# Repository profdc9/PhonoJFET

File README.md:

# Phono JFET Amplifier

This is a JFET amplifier suitable to be used with a piezo contact microphone.  It is being used with a mechanical record player, but it can also be used with as a contact microphone on an acoustic guitar, the brass bell of a horn, etc.

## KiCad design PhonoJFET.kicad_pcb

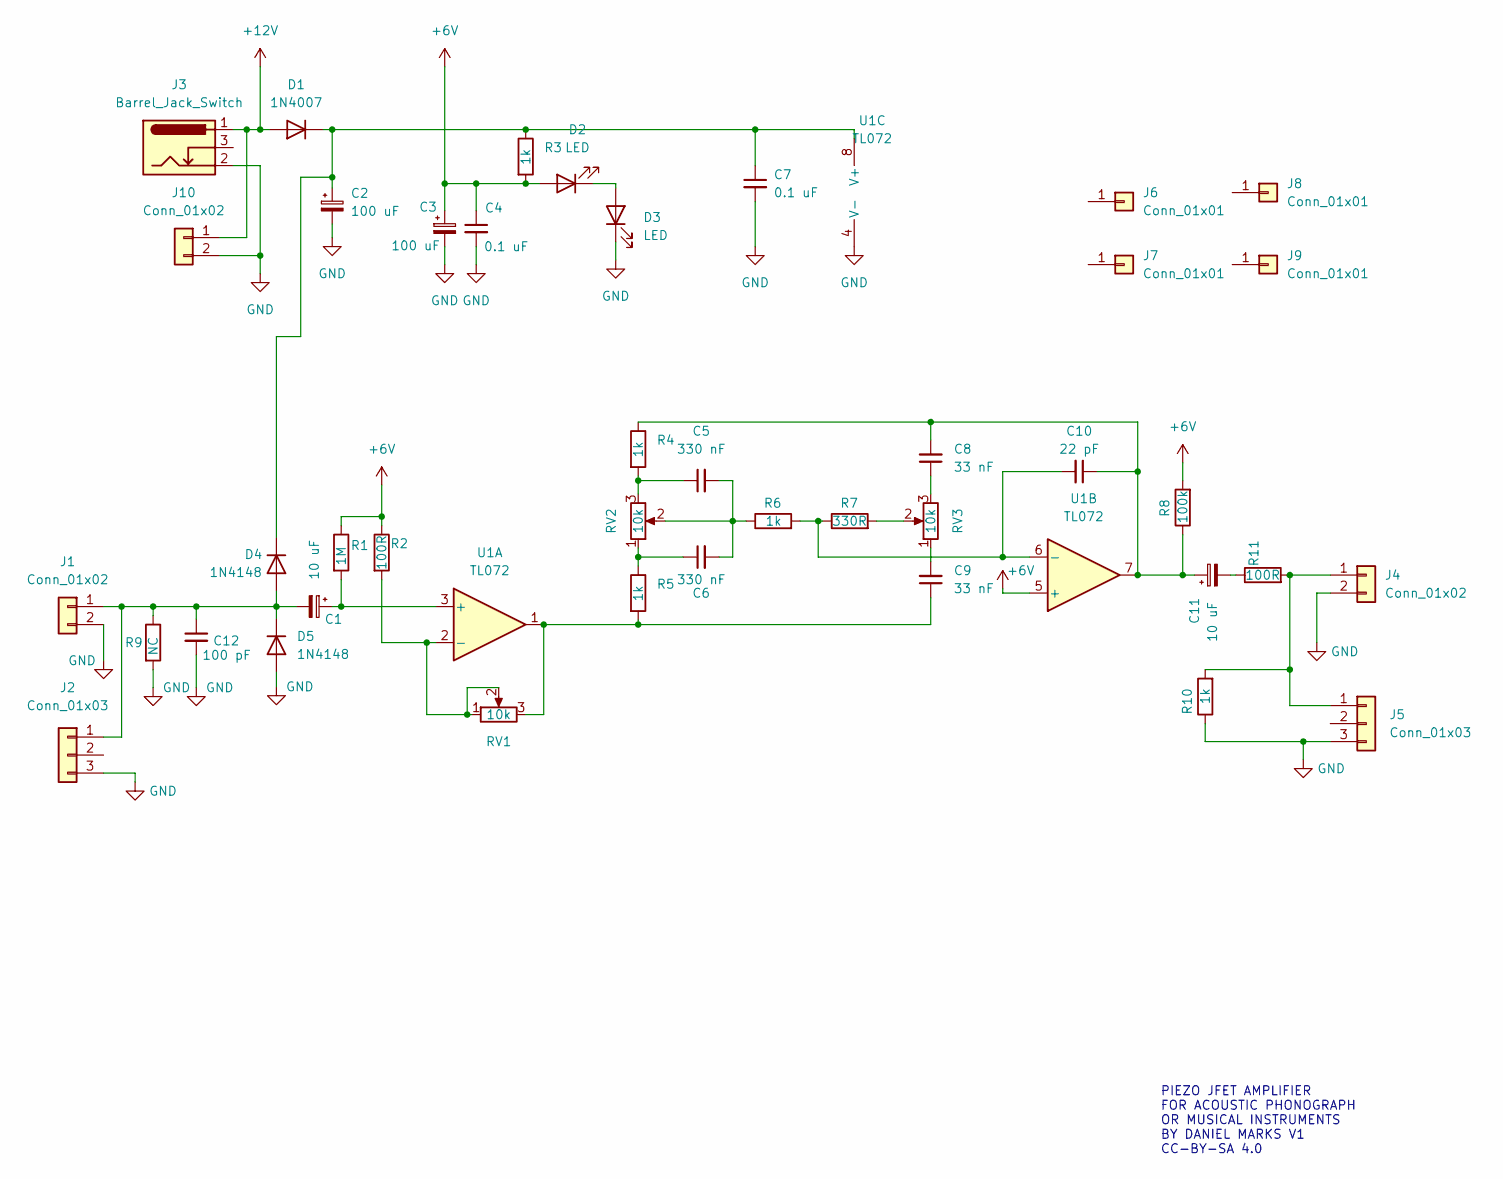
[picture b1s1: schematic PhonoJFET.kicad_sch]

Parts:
C1, C11: 10 uF; CP_Radial_D5.0mm_P2.50mm
C2, C3: 100 uF; CP_Radial_D5.0mm_P2.50mm
C4, C7: 0.1 uF; C_Disc_D5.0mm_W2.5mm_P5.00mm
C5, C6: 330 nF; C_Disc_D5.0mm_W2.5mm_P5.00mm
C8, C9: 33 nF; C_Disc_D5.0mm_W2.5mm_P5.00mm
C10: 22 pF; C_Disc_D5.0mm_W2.5mm_P5.00mm
C12: 100 pF; C_Disc_D5.0mm_W2.5mm_P5.00mm
D1: 1N4007; D_DO-41_SOD81_P7.62mm_Horizontal
D2, D3: LED; LED_D3.0mm
D4, D5: 1N4148; D_DO-41_SOD81_P7.62mm_Horizontal
J1, J4, J10: Conn_01x02; TerminalBlock_bornier-2_P5.08mm
J2, J5: Conn_01x03; PJ-3240-35mm-stereo
J3: Barrel_Jack_Switch; BarrelJack_Horizontal
J6, J7, J8, J9: Conn_01x01; Pin_D1.0mm_L10.0mm_LooseFit
R1: 1M; R_Axial_DIN0207_L6.3mm_D2.5mm_P7.62mm_Horizontal
R2, R11: 100R; R_Axial_DIN0207_L6.3mm_D2.5mm_P7.62mm_Horizontal
R3, R4, R5, R6, R10: 1k; R_Axial_DIN0207_L6.3mm_D2.5mm_P7.62mm_Horizontal
R7: 330R; R_Axial_DIN0207_L6.3mm_D2.5mm_P7.62mm_Horizontal
R8: 100k; R_Axial_DIN0207_L6.3mm_D2.5mm_P7.62mm_Horizontal
R9: NC; R_Axial_DIN0207_L6.3mm_D2.5mm_P7.62mm_Horizontal
RV1, RV2, RV3: 10k; Dual_Potentiometer_WirePads
U1: TL072; DIP-8_W7.62mm_Socket

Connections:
+6V: C3.1, C4.1, D2.2 (A), R1.1, R2.1, R3.2, R8.2, U1.5 (+)
+12V: D1.2 (A), J3.1, J10.1
GND: C2.2, C3.2, C4.2, C7.2, C12.2, D3.1 (K), D5.2 (A), J1.2, J2.3, J3.2, J4.2, J5.3, J10.2, R9.2, R10.1, U1.4 (V-)
unnamed: C1.1, R1.2, U1.3 (+)
unnamed: C1.2, C12.1, D4.2 (A), D5.1 (K), J1.1, J2.1, R9.1
unnamed: C2.1, C7.1, D1.1 (K), D4.1 (K), R3.1, U1.8 (V+)
unnamed: C5.1, R4.2, RV2.3
unnamed: C5.2, C6.2, R6.1, RV2.2
unnamed: C6.1, R5.1, RV2.1
unnamed: C8.1, RV3.3
unnamed: C9.1, R5.2, RV1.3, U1.1
unnamed: C9.2, RV3.1
unnamed: C8.2, C10.1, C11.1, R4.1, R8.1, U1.7
unnamed: C10.2, R6.2, R7.1, U1.6 (-)
unnamed: C11.2, R11.1
unnamed: D2.1 (K), D3.2 (A)
unnamed: J4.1, J5.1, R10.2, R11.2
unnamed: R2.2, RV1.1, RV1.2, U1.2 (-)
unnamed: R7.2, RV3.2

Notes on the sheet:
PIEZO JFET AMPLIFIER FOR ACOUSTIC PHONOGRAPH OR MUSICAL INSTRUMENTS BY DANIEL MARKS V1 CC-BY-SA 4.0

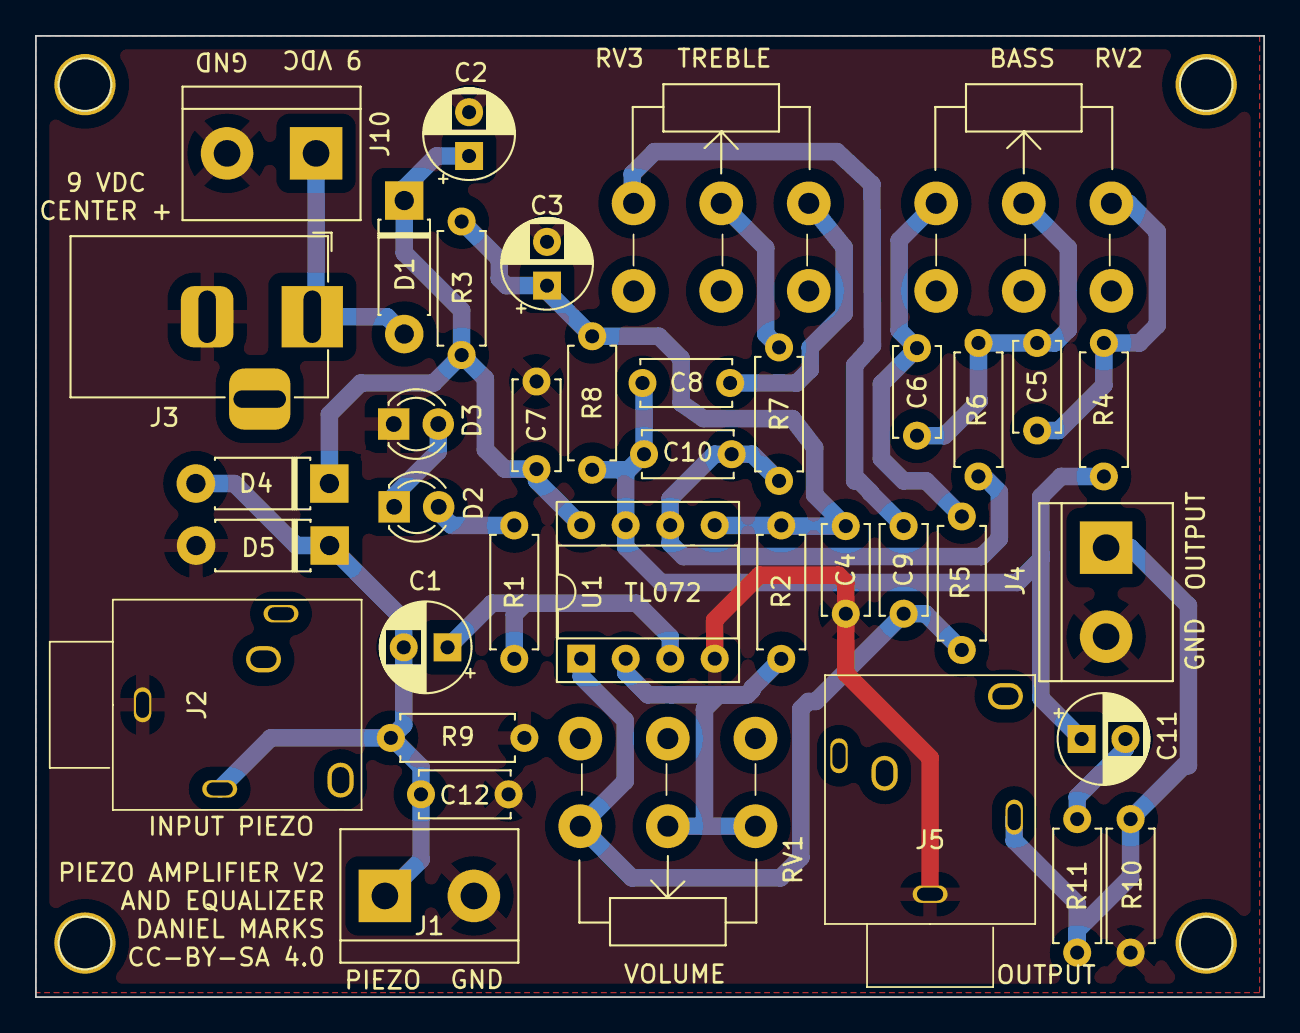
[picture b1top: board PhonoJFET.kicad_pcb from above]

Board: 2 copper layers, 70.1 x 54.9 mm, 42 parts (0 on the bottom side), 19 nets.

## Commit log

2022-04-13 Fixed some component values and biases
2022-04-20 Modified pcb
